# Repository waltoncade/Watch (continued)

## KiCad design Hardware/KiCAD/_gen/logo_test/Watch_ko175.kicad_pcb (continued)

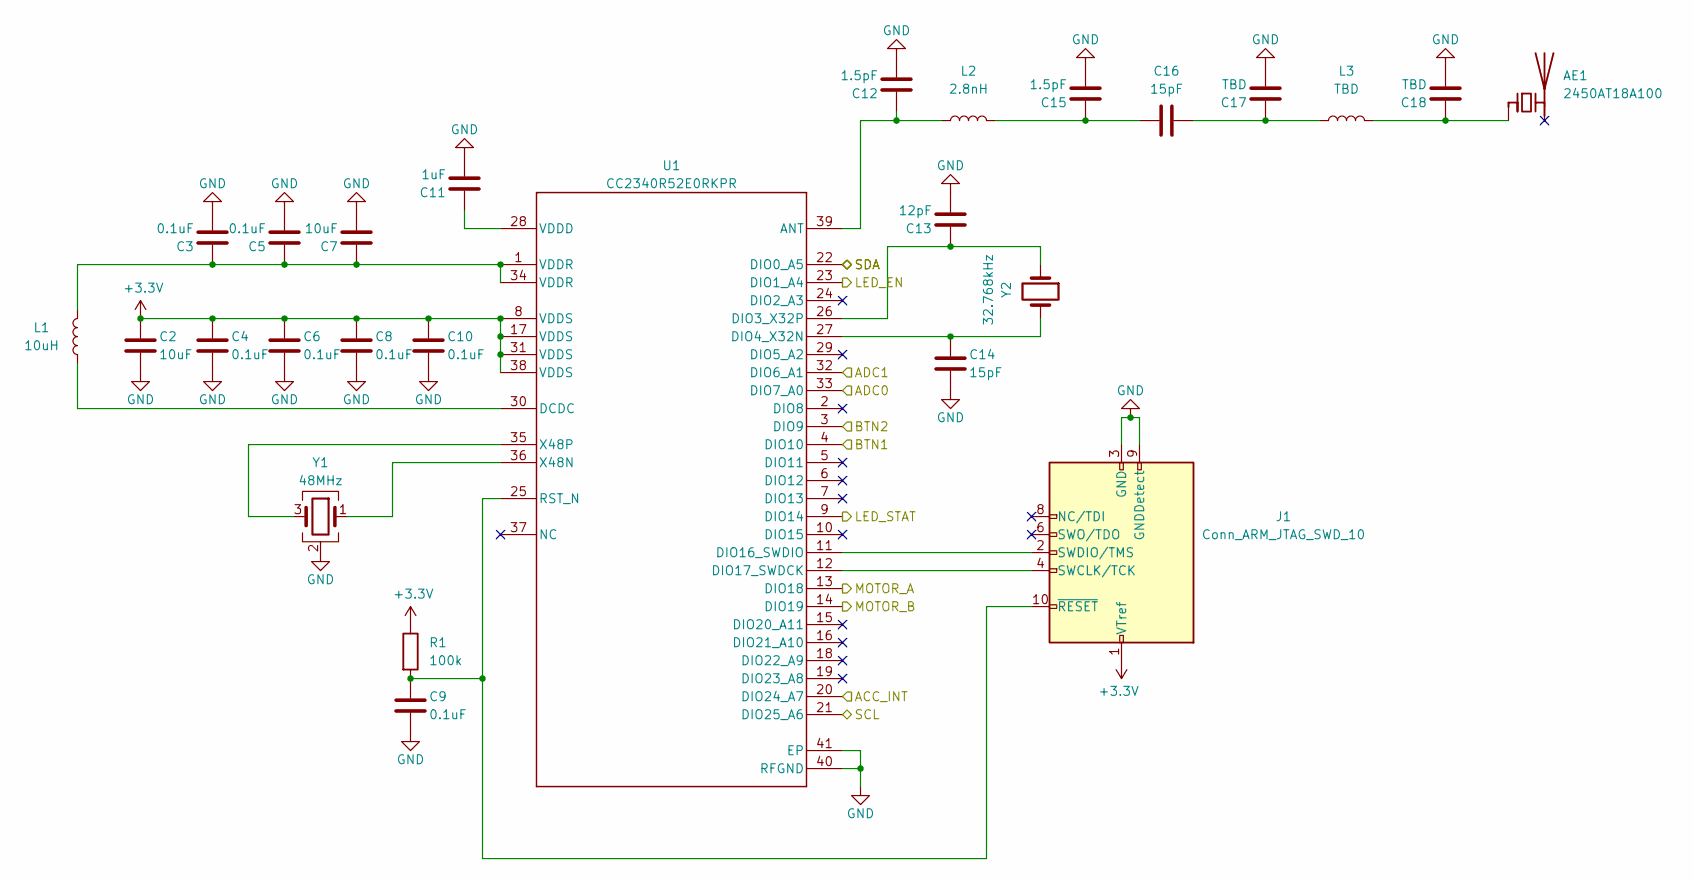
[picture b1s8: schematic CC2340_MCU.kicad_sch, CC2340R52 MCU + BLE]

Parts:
AE1: 2450AT18A100; Johanson_2450AT18x100; MPN Johanson 2450AT18A100 (placeholder, TBD)
C2, C7: 10uF; C_0402_1005Metric
C3, C4, C5, C6, C8, C9, C10: 0.1uF; C_0402_1005Metric
C11: 1uF; C_0402_1005Metric
C12, C15: 1.5pF; C_0402_1005Metric
C13: 12pF; C_0402_1005Metric
C14, C16: 15pF; C_0402_1005Metric
C17, C18: TBD; C_0402_1005Metric
J1: Conn_ARM_JTAG_SWD_10; PinHeader_2x05_P1.27mm_Vertical_SMD
L1: 10uH; L_0603_1608Metric; MPN MLZ1608N100LT000 (TI E2E-tested 0603 al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
L2: 2.8nH; L_0402_1005Metric
L3: TBD; L_0402_1005Metric
R1: 100k; R_0402_1005Metric
U1: CC2340R52E0RKPR; RKP0040B-IPC_B
Y1: 48MHz; Crystal_SMD_2016-4Pin_2.0x1.6mm; MPN TZ3908AAAO43
Y2: 32.768kHz; Crystal_SMD_2012-2Pin_2.0x1.2mm; MPN TBD (CL 6-12pF per SWRS272F CC2340R5 da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

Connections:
+3.3V: C2.1, C4.1, C6.1, C8.1, C10.1, J1.1 (VTref), R1.1, U1.8 (VDDS), U1.17 (VDDS), U1.31 (VDDS), U1.38 (VDDS); also elsewhere on the board
/ACC_INT: U1.20 (DIO24_A7); also elsewhere on the board
/LED_EN: U1.23 (DIO1_A4); also elsewhere on the board
/MCU/LED_STAT: U1.9 (DIO14); also elsewhere on the board
/MCU/MOTOR_A: U1.13 (DIO18); also elsewhere on the board
/MCU/MOTOR_B: U1.14 (DIO19); also elsewhere on the board
/SW1: U1.4 (DIO10); also elsewhere on the board
/SW2: U1.3 (DIO9); also elsewhere on the board
/bSense: U1.33 (DIO7_A0); also elsewhere on the board
/leds/SCL: U1.21 (DIO25_A6); also elsewhere on the board
/leds/SDA: U1.22 (DIO0_A5); also elsewhere on the board
/vLUX: U1.32 (DIO6_A1); also elsewhere on the board
GND: C2.2, C3.2, C4.2, C5.2, C6.2, C7.2, C8.2, C9.2, C10.2, C11.2, C12.2, C13.2, C14.2, C15.2, C17.2, C18.2, J1.3 (GND), J1.5 (GND), J1.9 (GNDDetect), U1.40 (RFGND), U1.41 (EP), Y1.2 (G), Y1.4 (G); also elsewhere on the board
unnamed: AE1.1 (FEED_1), C18.1, L3.2
unnamed: C3.1, C5.1, C7.1, L1.2, U1.1 (VDDR), U1.34 (VDDR)
unnamed: C15.1, C16.1, L2.2
unnamed: C16.2, C17.1, L3.1
unnamed 50: J1.4 (SWCLK/TCK), U1.12 (DIO17_SWDCK); also elsewhere on the board
unnamed 51: J1.2 (SWDIO/TMS), U1.11 (DIO16_SWDIO); also elsewhere on the board
unnamed: C12.1, L2.1, U1.39 (ANT)
unnamed: L1.1, U1.30 (DCDC)
unnamed: C13.1, U1.26 (DIO3_X32P), Y2.1
unnamed: C14.1, U1.27 (DIO4_X32N), Y2.2
unnamed: C11.1, U1.28 (VDDD)
unnamed: U1.36 (X48N), Y1.1
unnamed: U1.35 (X48P), Y1.3

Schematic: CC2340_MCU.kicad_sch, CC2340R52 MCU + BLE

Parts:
AE1: 2450AT18A100; Johanson_2450AT18x100; MPN Johanson 2450AT18A100 (placeholder, TBD)
C2, C7: 10uF; C_0402_1005Metric
C3, C4, C5, C6, C8, C9, C10: 0.1uF; C_0402_1005Metric
C11: 1uF; C_0402_1005Metric
C12, C15: 1.5pF; C_0402_1005Metric
C13: 12pF; C_0402_1005Metric
C14, C16: 15pF; C_0402_1005Metric
C17, C18: TBD; C_0402_1005Metric
L1: 10uH; L_0603_1608Metric; MPN MLZ1608N100LT000 (TI E2E-tested 0603 al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
L2: 2.8nH; L_0402_1005Metric
L3: TBD; L_0402_1005Metric
R1: 100k; R_0402_1005Metric
TP1: SWDIO; TestPoint_Pad_D1.0mm
TP2: SWCLK; TestPoint_Pad_D1.0mm
TP3: RESET; TestPoint_Pad_D1.0mm
TP4: 3V3; TestPoint_Pad_D1.0mm
TP5: GND; TestPoint_Pad_D1.0mm
U1: CC2340R52E0RKPR; RKP0040B-IPC_B
Y1: 48MHz; Crystal_SMD_2016-4Pin_2.0x1.6mm; MPN TZ3908AAAO43
Y2: 32.768kHz; Crystal_SMD_2012-2Pin_2.0x1.2mm; MPN TBD (CL 6-12pF per SWRS272F CC2340R5 da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

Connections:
+3.3V: C2.1, C4.1, C6.1, C8.1, C10.1, R1.1, TP4.1, U1.8 (VDDS), U1.17 (VDDS), U1.31 (VDDS), U1.38 (VDDS); also elsewhere on the board
/ACC_INT: U1.20 (DIO24_A7); also elsewhere on the board
/LED_EN: U1.23 (DIO1_A4); also elsewhere on the board
/MCU/LED_STAT: U1.9 (DIO14); also elsewhere on the board
/MCU/MOTOR_A: U1.13 (DIO18); also elsewhere on the board
/MCU/MOTOR_B: U1.14 (DIO19); also elsewhere on the board
/SW1: U1.4 (DIO10); also elsewhere on the board
/SW2: U1.3 (DIO9); also elsewhere on the board
/bSense: U1.33 (DIO7_A0); also elsewhere on the board
/leds/SCL: U1.21 (DIO25_A6); also elsewhere on the board
/leds/SDA: U1.22 (DIO0_A5); also elsewhere on the board
/vLUX: U1.32 (DIO6_A1); also elsewhere on the board
GND: C2.2, C3.2, C4.2, C5.2, C6.2, C7.2, C8.2, C9.2, C10.2, C11.2, C12.2, C13.2, C14.2, C15.2, C17.2, C18.2, TP5.1, U1.40 (RFGND), U1.41 (EP), Y1.2 (G), Y1.4 (G); also elsewhere on the board
unnamed: AE1.1 (FEED_1), C18.1, L3.2
unnamed: C3.1, C5.1, C7.1, L1.2, U1.1 (VDDR), U1.34 (VDDR)
unnamed: C15.1, C16.1, L2.2
unnamed: C16.2, C17.1, L3.1
unnamed 50: TP2.1, U1.12 (DIO17_SWDCK); also elsewhere on the board
unnamed 51: TP1.1, U1.11 (DIO16_SWDIO); also elsewhere on the board
unnamed: C12.1, L2.1, U1.39 (ANT)
unnamed: L1.1, U1.30 (DCDC)
unnamed: C13.1, U1.26 (DIO3_X32P), Y2.1
unnamed: C14.1, U1.27 (DIO4_X32N), Y2.2
unnamed: C11.1, U1.28 (VDDD)
unnamed: U1.36 (X48N), Y1.1
unnamed: U1.35 (X48P), Y1.3

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
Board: 4 copper layers, 89 parts (51 on the bottom side), 63 nets, no tracks yet.

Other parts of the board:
D501, D502: BAT54S; SOT-23
H1: Hand shaft 2.3mm NPTH; NPTH_2.0mm_HandShaft
LOGO1: W_Logo
R501, R502: 1.2k; R_0402_1005Metric
TP501: TP_COIL_A; TestPoint_Pad_1.5x1.5mm
TP502: TP_COIL_B; TestPoint_Pad_1.5x1.5mm

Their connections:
+3.3V: D501.2 (K), D502.2 (K); also elsewhere on the board
/MCU/MOTOR_A: R501.1; also elsewhere on the board
/MCU/MOTOR_B: R502.1; also elsewhere on the board
GND: D501.1 (A), D502.1 (A); also elsewhere on the board
unnamed: D501.3 (COM), R501.2, TP501.1 (1_1)
unnamed: D502.3 (COM), R502.2, TP502.1 (1_1)
